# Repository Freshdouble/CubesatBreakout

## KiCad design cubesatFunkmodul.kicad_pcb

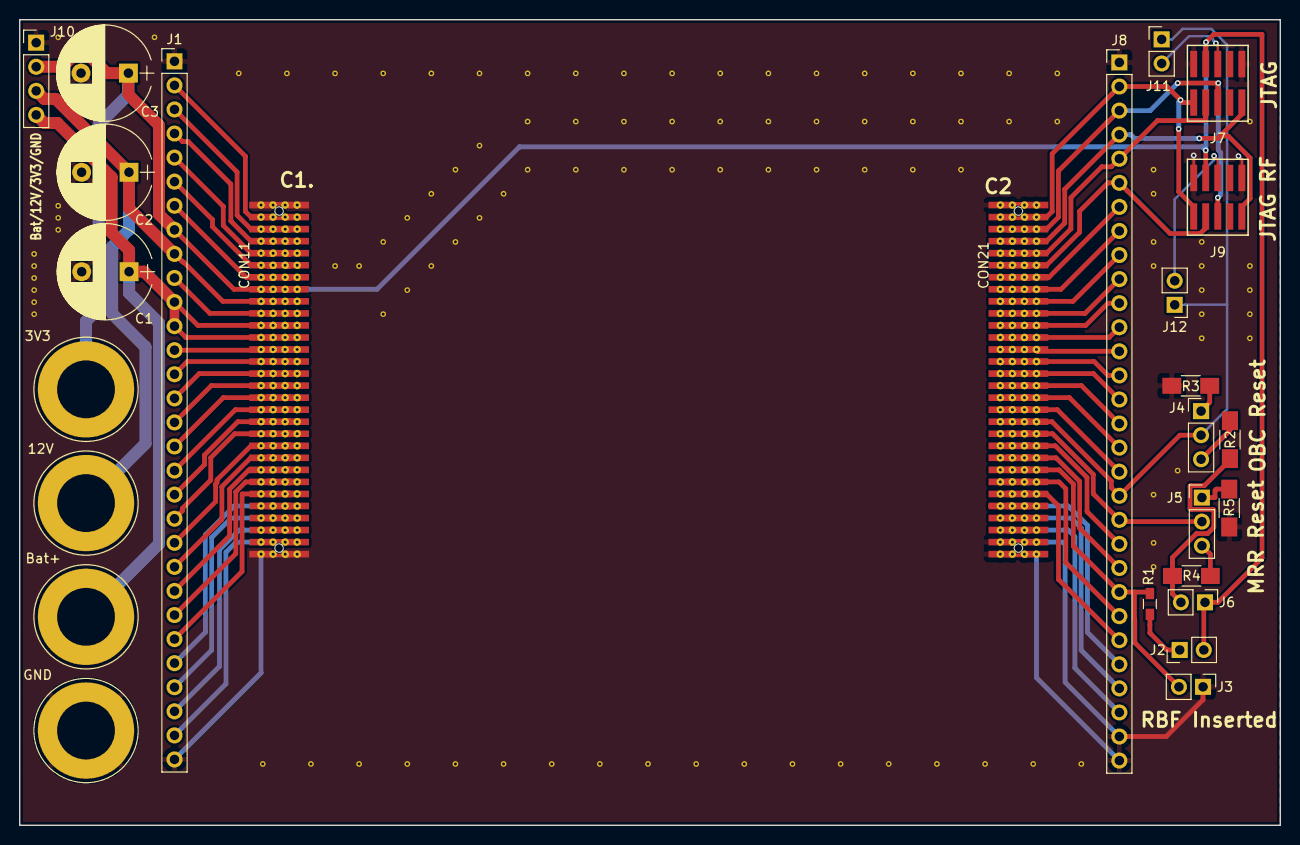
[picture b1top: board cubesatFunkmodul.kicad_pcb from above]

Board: 2 copper layers, 133.0 x 85.0 mm, 26 parts (0 on the bottom side), 63 nets.

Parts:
3V3, 12V: Conn_01x01; Banana_Jack_1Pin
Bat+: Conn_01x01; Banana_Jack_1Pin
C1, C2, C3: CP; CP_Radial_D10.0mm_P5.00mm
CON11: DISCO-CON1; Cubesatconnector
CON21: DISCO-CON2; Cubesatconnector
GND: Conn_01x01; Banana_Jack_1Pin
J1, J8: Conn_01x30; Pin_Header_Straight_1x30_Pitch2.54mm
J2, J3, J6, J11, J12: Conn_01x02; Pin_Header_Straight_1x02_Pitch2.54mm
J4, J5: Conn_01x03; Pin_Header_Straight_1x03_Pitch2.54mm
J7, J9: Conn_02x05_Odd_Even; FTSH-105-01-L-DV-K
J10: Conn_01x03; Pin_Header_Straight_1x04_Pitch2.54mm
R1: 10k; R_0603_HandSoldering
R2, R3, R4, R5: R; R_1206_HandSoldering

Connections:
+3V3: 3V3.1, C3.1, CON11.8, J1.8, J2.2, J6.1, J7.4, J9.4, J10.2
/Connector/12V: 12V.1, C2.1, CON11.9, J1.9, J10.3
/Connector/BAT+: Bat+.1, C1.1, CON11.11, CON11.12, J1.11, J1.12, J10.4
/Connector/TCK: CON21.2, J7.1, J8.2, J9.1
/Connector/TDI: CON21.4, J7.9, J8.4, J9.9
/Connector/TDO: CON21.5, J7.3, J8.5
/Connector/TDO-RF: CON21.6, J8.6, J9.3
/Connector/TMS: CON21.3, J7.5, J8.3, J9.5
/Connector/~OBC_RESET~: CON21.19, J4.2, J8.19, J11.1, J12.1
GND: C1.2, C2.2, C3.2, CON11.1, CON11.30, CON21.1, CON21.29, CON21.30, GND.1, J1.1, J1.30, J3.1, J7.2, J7.10, J8.1, J8.29, J8.30, J9.2, J9.10, J10.1, R3.1, R5.1
unnamed: CON11.2, J1.2
unnamed: CON11.3, J1.3
unnamed: CON11.4, J1.4
unnamed: CON11.5, J1.5
unnamed: CON11.6, J1.6
unnamed: CON11.7, J1.7
unnamed: CON11.10, J1.10
unnamed: CON11.13, J1.13
unnamed: CON11.14, J1.14
unnamed: CON11.15, J1.15
unnamed: CON11.16, J1.16
unnamed: CON11.17, J1.17
unnamed: CON11.18, J1.18
unnamed: CON11.19, J1.19
unnamed: CON11.20, J1.20
unnamed: CON11.21, J1.21
unnamed: CON11.22, J1.22
unnamed: CON11.23, J1.23
unnamed: CON11.24, J1.24
unnamed: CON11.25, J1.25
unnamed: CON11.26, J1.26
unnamed: CON11.27, J1.27
unnamed: CON11.28, J1.28
unnamed: CON11.29, J1.29
unnamed: CON21.7, J8.7
unnamed: CON21.8, J8.8
unnamed: CON21.9, J8.9
unnamed: CON21.10, J8.10
unnamed: CON21.11, J8.11
unnamed: CON21.12, J8.12
unnamed: CON21.13, J8.13
unnamed: CON21.14, J8.14
unnamed: CON21.15, J8.15
unnamed: CON21.16, J8.16
unnamed: CON21.17, J8.17
unnamed: CON21.18, J8.18
unnamed: CON21.20, J5.2, J8.20
unnamed: CON21.21, J8.21
unnamed: CON21.22, J8.22
unnamed: CON21.23, J3.2, J8.23, R1.2
unnamed: CON21.24, J8.24
unnamed: CON21.25, J8.25
unnamed: CON21.26, J8.26
unnamed: CON21.27, J8.27
unnamed: CON21.28, J8.28
unnamed: J2.1, R1.1
unnamed: J4.1, R3.2
unnamed: J4.3, R2.2
unnamed: J5.1, R5.2
unnamed: J5.3, R4.2
unnamed: J6.2, R2.1, R4.1
unnamed: J7.6, J11.2
unnamed: J9.6, J12.2
